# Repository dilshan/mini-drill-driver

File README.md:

# Replacement motor driver for INGCO mini drills

This is replacement motor driver for [INGCO](http://ingcotools.com) mini drills / die grinders. This project is mainly developed to replace motor speed controller of the *INGCO  MG1502.2* mini drill. 

This speed controller is designed based on Microchip [PIC12F629](https://www.microchip.com/wwwproducts/en/PIC12F629) 8-bit CMOS microcontroller.  This MCU is used for zero-crossing detection, determine TRIAC firing times and to handle buttons and switches.

As an original board, the controller supply comes from the mains through a simple RCD circuit. 

The firmware of this controller is design to operate with 4MHz internal-oscillator of the MCU. The current version of this controller is designed to work with 50Hz AC power sources. For 60Hz, *TIMER0* timing value needs to be changed in the firmware source code. 

Compare with the original *MG1502.2* controller board this controller is not equipped with LCD. We remove LCD from this design due to the unavailability of compatibaly LCD modules. Also, we design this controller using commonly available through-hole type components.  

**WARNING:** This controller board is powered by AC mains voltage. Avoid touching the board when power is applied. If possible, use an isolation transformer for the testing.

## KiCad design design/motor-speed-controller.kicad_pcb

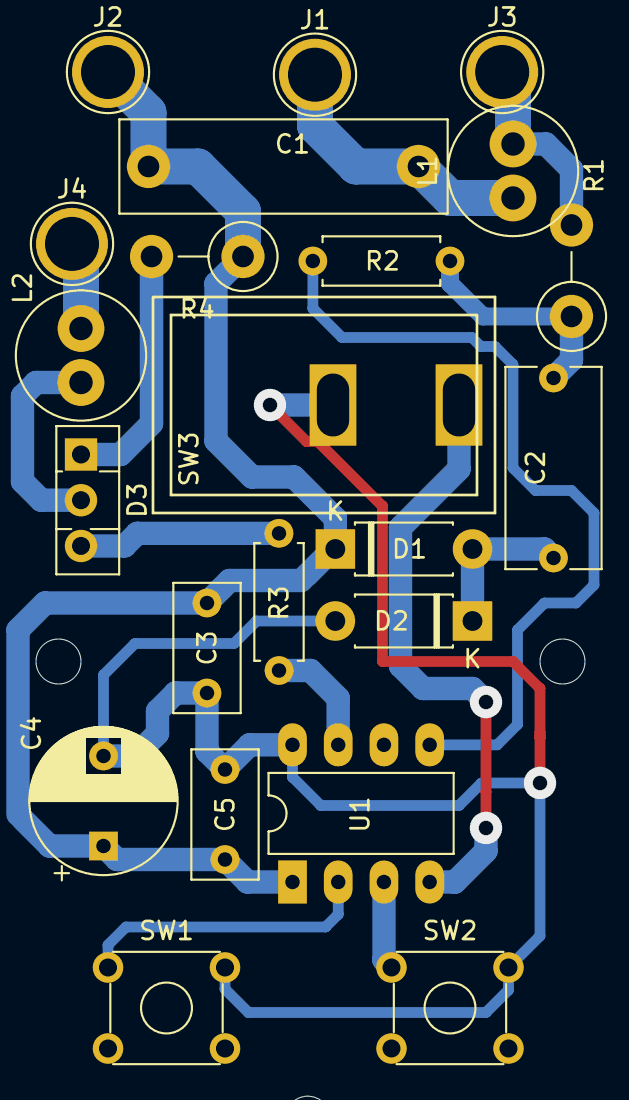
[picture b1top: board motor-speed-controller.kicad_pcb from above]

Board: 2 copper layers, 25 parts (0 on the bottom side), 15 nets.

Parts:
C1: 0.27MFD; C_Rect_L18.0mm_W5.0mm_P15.00mm_FKS3_FKP3
C2: 0.1MFD; C_Rect_L11.0mm_W5.1mm_P10.00mm_MKT
C3, C5: 0.1MFD; C_Rect_L7.0mm_W3.5mm_P5.00mm
C4: 220MFD; CP_Radial_D8.0mm_P5.00mm
D1: 1N4733A; D_DO-41_SOD81_P7.62mm_Horizontal
D2: 1N4007; D_DO-41_SOD81_P7.62mm_Horizontal
D3: BT134-600; TO-126-3_Vertical
H1, H2, H3: MountingHole_2.5mm
J1, J2: AC-IN1; TestPoint_Plated_Hole_D3.0mm
J3: MOTOR-1; TestPoint_Plated_Hole_D3.0mm
J4: MOTOR-2; TestPoint_Plated_Hole_D3.0mm
L1, L2: 1mH; L_Radial_D7.0mm_P3.00mm
R1: 390R; R_Axial_DIN0411_L9.9mm_D3.6mm_P5.08mm_Vertical
R2: 1M; R_Axial_DIN0207_L6.3mm_D2.5mm_P7.62mm_Horizontal
R3: 100R; R_Axial_DIN0207_L6.3mm_D2.5mm_P7.62mm_Horizontal
R4: 0.22R; R_Axial_DIN0411_L9.9mm_D3.6mm_P5.08mm_Vertical
SW1: DOWN; SW_TH_Tactile_Omron_B3F-10xx
SW2: UP; SW_TH_Tactile_Omron_B3F-10xx
SW3: POWER; SWITCH-SPST
U1: PIC12F629-IP; DIP-8_W7.62mm_LongPads

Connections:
GND: C3.2, C4.2, C5.2, D2.2, SW1.2, SW2.2, SW3.2, U1.8
unnamed: C1.1, C3.1, C4.1, C5.1, D1.1, J2.1, R4.1, U1.1
unnamed: C1.2, J1.1, L1.1
unnamed: C2.1, D1.2, D2.1
unnamed: C2.2, R1.1, R2.2
unnamed: D3.1, R4.2
unnamed: D3.2, L2.2
unnamed: D3.3, R3.2
unnamed: J3.1, L1.2, R1.2
unnamed: J4.1, L2.1
unnamed: R2.1, U1.5
unnamed: R3.1, U1.7
unnamed: SW1.1, U1.2
unnamed: SW2.1, U1.3
unnamed: SW3.1, U1.4

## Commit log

2019-04-04 Initial commit with source and design files.
2019-04-04 Update documentation with images and links.
